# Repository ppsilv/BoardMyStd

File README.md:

# BoardMyStd
Standard board with euro connector 96 pins.

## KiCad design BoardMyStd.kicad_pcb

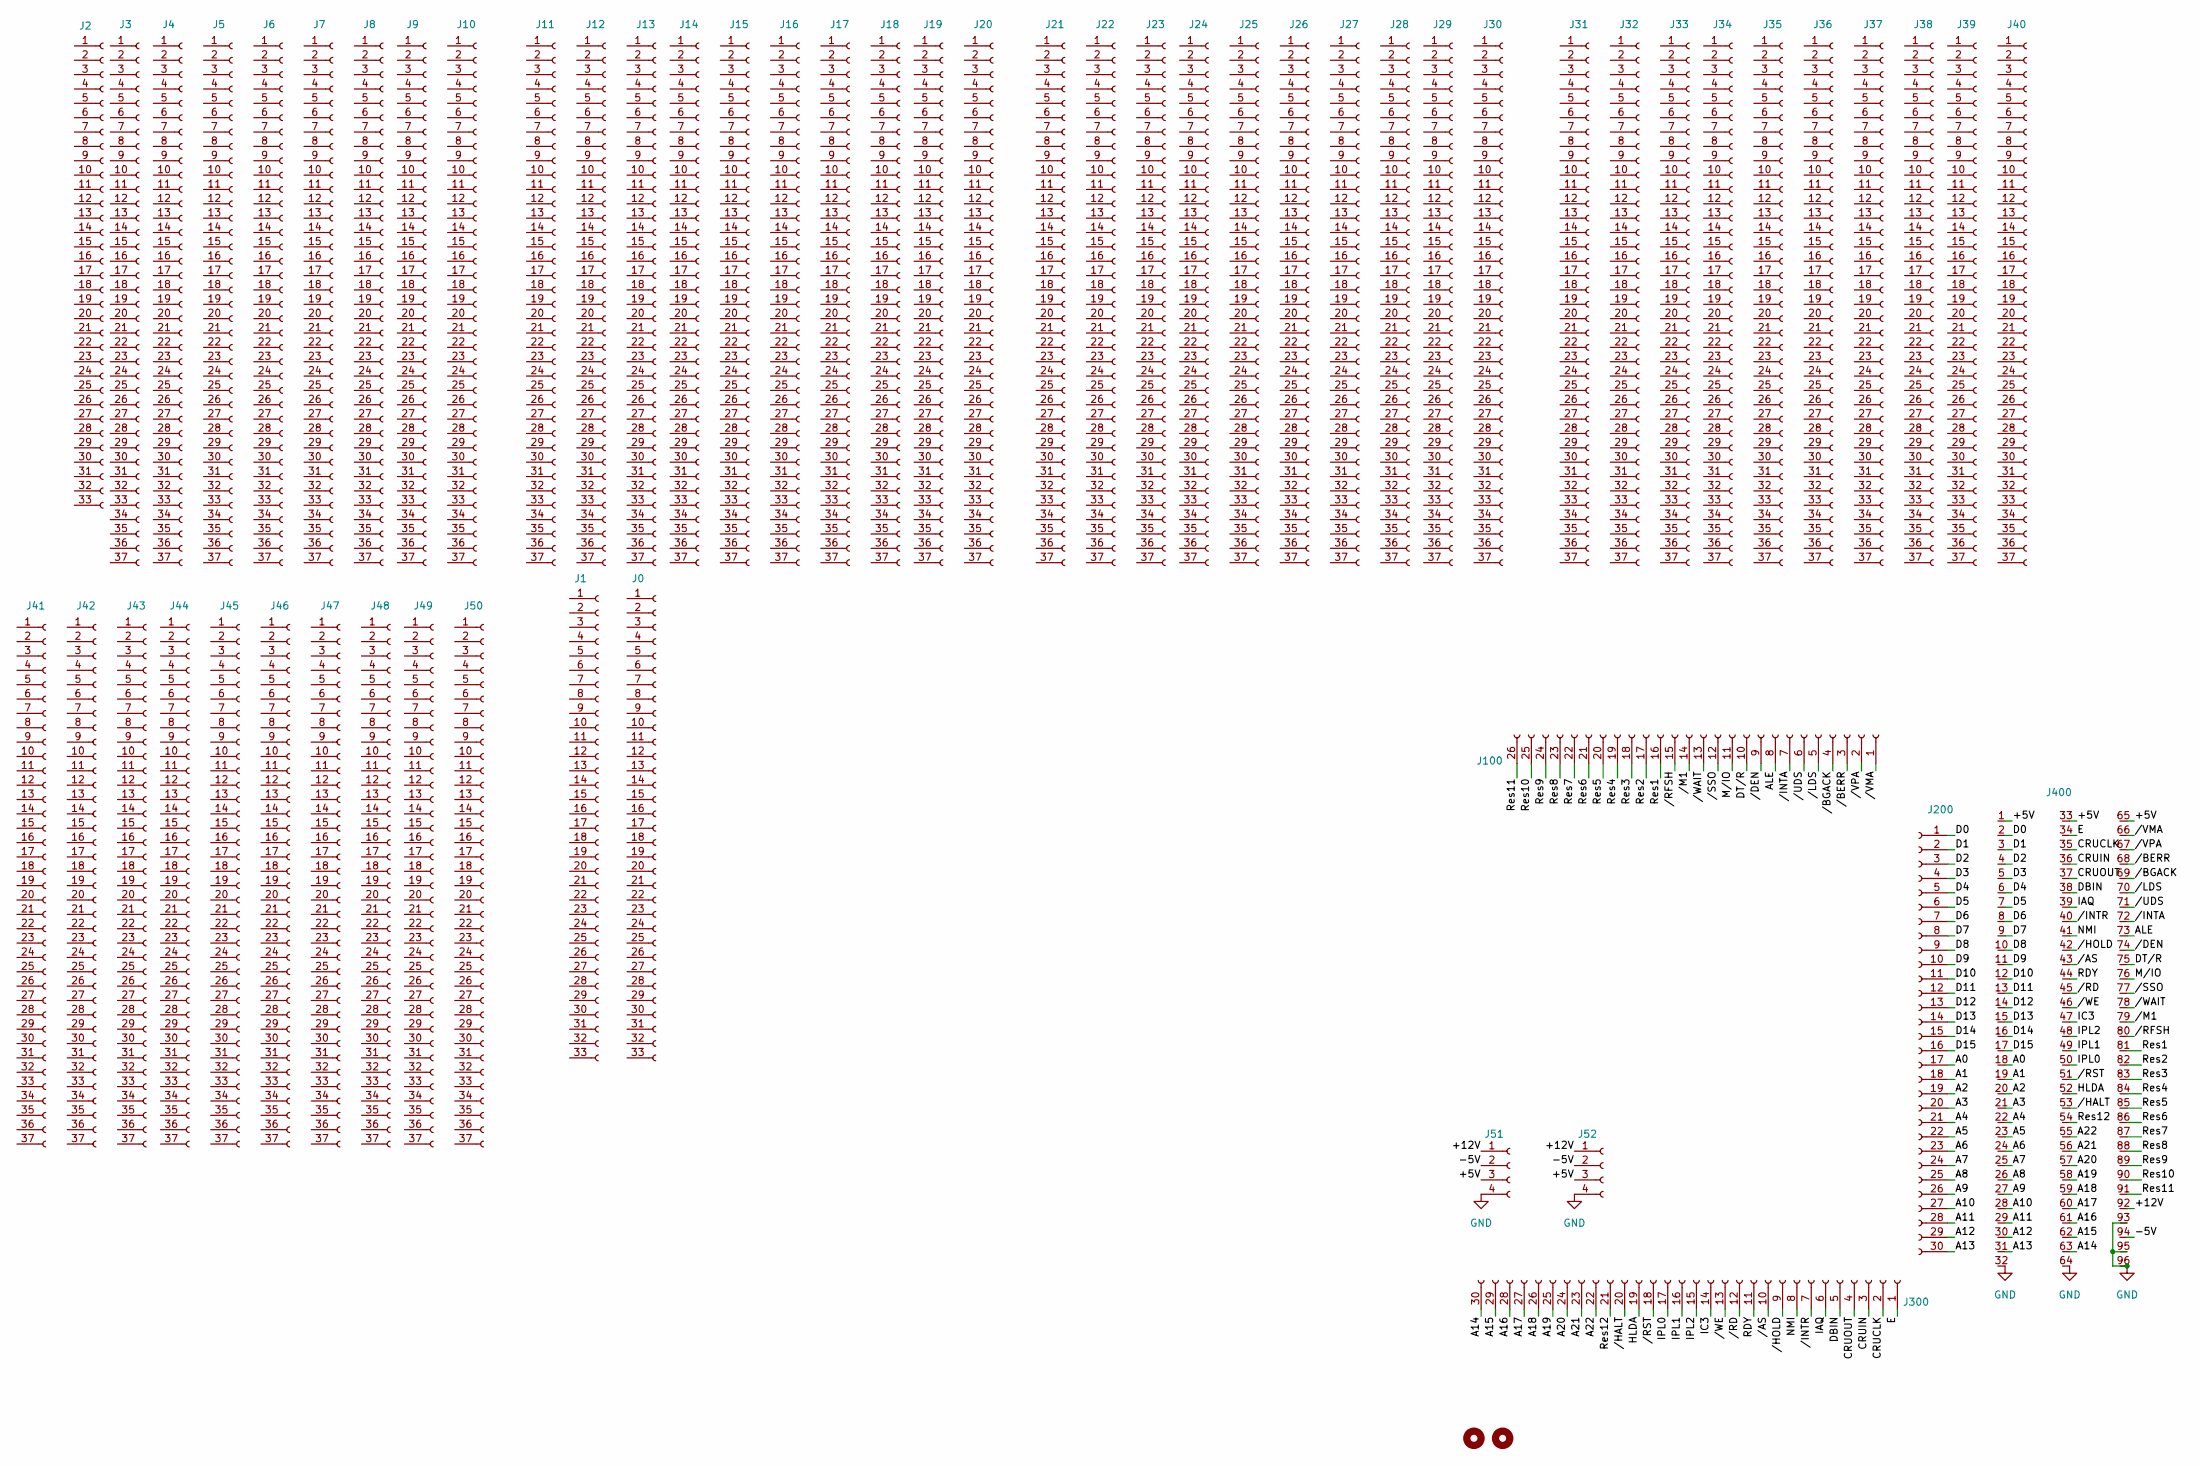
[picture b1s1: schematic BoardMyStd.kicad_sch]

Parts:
H1, H2: MountingHole; MountingHole_3.2mm_M3
J0, J1, J2: Conn_01x33_Socket; PinHeader_1x33_P2.54mm_Vertical
J3, J4, J5, J6, J7, J8, J9, J10, J11, J12, J13, J14, J15, J16, J17, J18, J19, J20, J21, J22, J23, J24, J25, J26, J27, J28, J29, J30, J31, J32, J33, J34, J35, J36, J37, J38, J39, J40, J41, J42, J43, J44, J45, J46, J47, J48, J49, J50: Conn_01x37_Socket; PinHeader_1x37_P2.54mm_Vertical
J51, J52: Conn_01x04_Socket; PinHeader_1x04_P2.54mm_Vertical
J100: Conn_01x26_Socket; PinSocket_1x26_P2.54mm_Vertical
J200, J300: Conn_01x30_Socket; PinSocket_1x30_P2.54mm_Vertical
J400: conn_euro96

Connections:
/+5V: J51.3, J52.3, J400.1, J400.33, J400.65
/+12V: J51.1, J52.1, J400.92
/-5V: J51.2, J52.2, J400.94
/A0: J200.17, J400.18
/A1: J200.18, J400.19
/A2: J200.19, J400.20
/A3: J200.20, J400.21
/A4: J200.21, J400.22
/A5: J200.22, J400.23
/A6: J200.23, J400.24
/A7: J200.24, J400.25
/A8: J200.25, J400.26
/A9: J200.26, J400.27
/A10: J200.27, J400.28
/A11: J200.28, J400.29
/A12: J200.29, J400.30
/A13: J200.30, J400.31
/A14: J300.30, J400.63
/A15: J300.29, J400.62
/A16: J300.28, J400.61
/A17: J300.27, J400.60
/A18: J300.26, J400.59
/A19: J300.25, J400.58
/A20: J300.24, J400.57
/A21: J300.23, J400.56
/A22: J300.22, J400.55
/ALE: J100.8, J400.73
/CRUCLK: J300.2, J400.35
/CRUIN: J300.3, J400.36
/CRUOUT: J300.4, J400.37
/D0: J200.1, J400.2
/D1: J200.2, J400.3
/D2: J200.3, J400.4
/D3: J200.4, J400.5
/D4: J200.5, J400.6
/D5: J200.6, J400.7
/D6: J200.7, J400.8
/D7: J200.8, J400.9
/D8: J200.9, J400.10
/D9: J200.10, J400.11
/D10: J200.11, J400.12
/D11: J200.12, J400.13
/D12: J200.13, J400.14
/D13: J200.14, J400.15
/D14: J200.15, J400.16
/D15: J200.16, J400.17
/DBIN: J300.5, J400.38
/DT/R: J100.10, J400.75
/E: J300.1, J400.34
/HLDA: J300.19, J400.52
/IAQ: J300.6, J400.39
/IC3: J300.14, J400.47
/IPL0: J300.17, J400.50
/IPL1: J300.16, J400.49
/IPL2: J300.15, J400.48
/M/IO: J100.11, J400.76
/NMI: J300.8, J400.41
/RDY: J300.11, J400.44
/Res1: J100.16, J400.81
/Res2: J100.17, J400.82
/Res3: J100.18, J400.83
/Res4: J100.19, J400.84
/Res5: J100.20, J400.85
/Res6: J100.21, J400.86
/Res7: J100.22, J400.87
/Res8: J100.23, J400.88
/Res9: J100.24, J400.89
/Res10: J100.25, J400.90
/Res11: J100.26, J400.91
/Res12: J300.21, J400.54
//AS: J300.10, J400.43
//BERR: J100.3, J400.68
//BGACK: J100.4, J400.69
//DEN: J100.9, J400.74
//HALT: J300.20, J400.53
//HOLD: J300.9, J400.42
//INTA: J100.7, J400.72
//INTR: J300.7, J400.40
//LDS: J100.5, J400.70
//M1: J100.14, J400.79
//RD: J300.12, J400.45
//RFSH: J100.15, J400.80
//RST: J300.18, J400.51
//SSO: J100.12, J400.77
//UDS: J100.6, J400.71
//VMA: J100.1, J400.66
//VPA: J100.2, J400.67
//WAIT: J100.13, J400.78
//WE: J300.13, J400.46
GND: J51.4, J52.4, J400.32, J400.64, J400.93, J400.95, J400.96

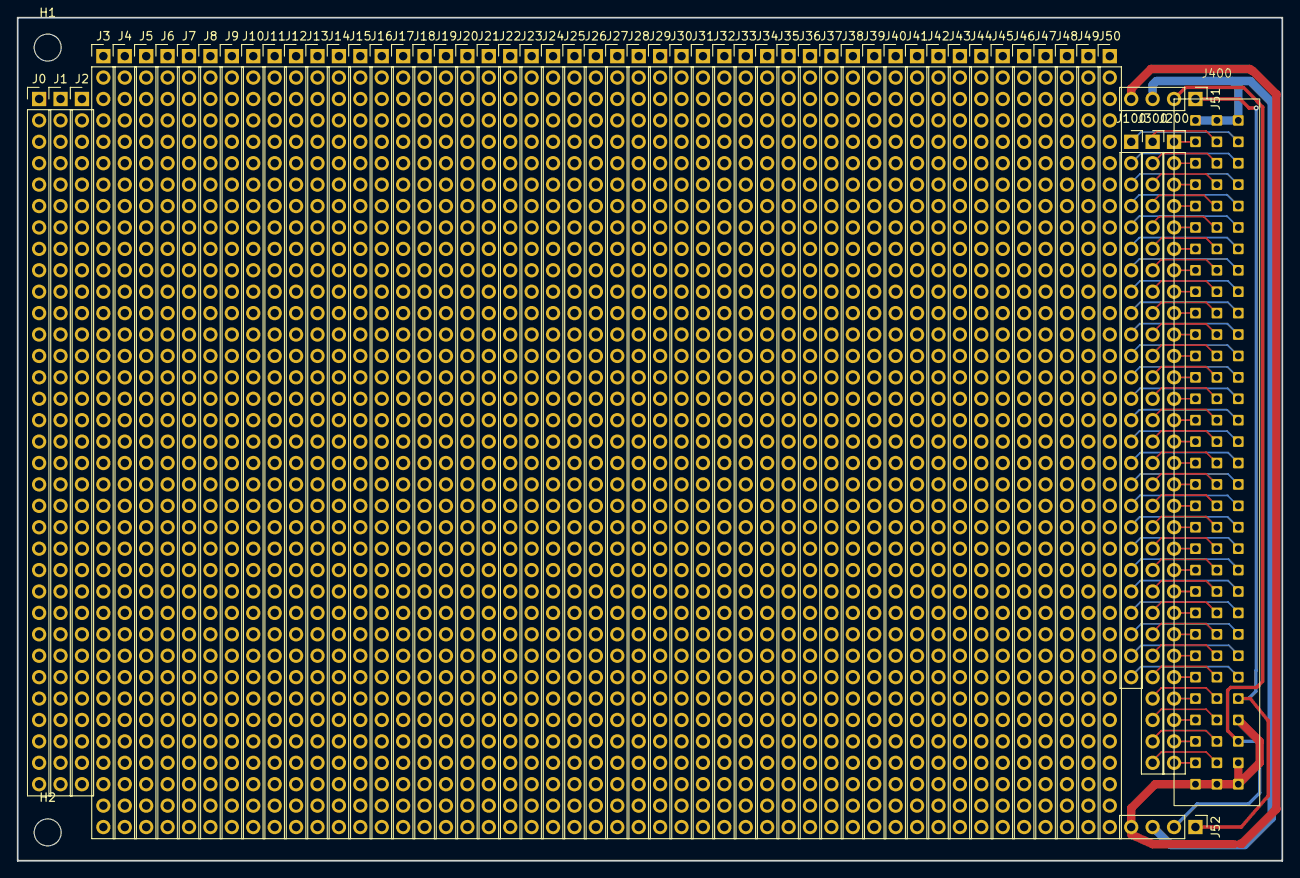
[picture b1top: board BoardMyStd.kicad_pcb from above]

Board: 2 copper layers, 150.0 x 100.0 mm, 59 parts (0 on the bottom side), 90 nets.
